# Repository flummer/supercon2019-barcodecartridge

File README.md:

# Barcode reader Cartridge for the 2019 Hackaday Superconference Badge

This is designed to use the GM65 barcode reader module, that supports both 1D and 2D barcodes and is able to read from a screen (eg. a smartphone or the screen on the badge)

This cartridge is based on the [unofficial Superconference 2019 Badge Cartridge template](https://github.com/flummer/supercon2019-cartridgetemplate) and hence include the w25q128 SPI flash and a 100nF cap in addition to the 2x20 pin angled male pin header for the badge connection. The flash allows badge configurations and firmware specific to this cartridge to be loaded from the cartridge it self making it selfcontained.

## Version 1.2 update

This updated version fixes an error in the pin connections on the cartridge connector (the two columns was flipped for some signals).

## Special note about the original version

If you want to use a PCB based on the original version with incorrect connections, it is possible to make a hardware hack on the 20x2 angeled header, where you move the pins around and bend some of them a bit, very precisely.

## License

The contents of this repository is released under the following licence:

 * the "Creative Commons Attribution-ShareAlike 4.0 International License"
   (CC BY-SA 4.0) full text of this license is included in the LICENSE file
   and a copy can also be found at
   http://creativecommons.org/licenses/by-sa/4.0/

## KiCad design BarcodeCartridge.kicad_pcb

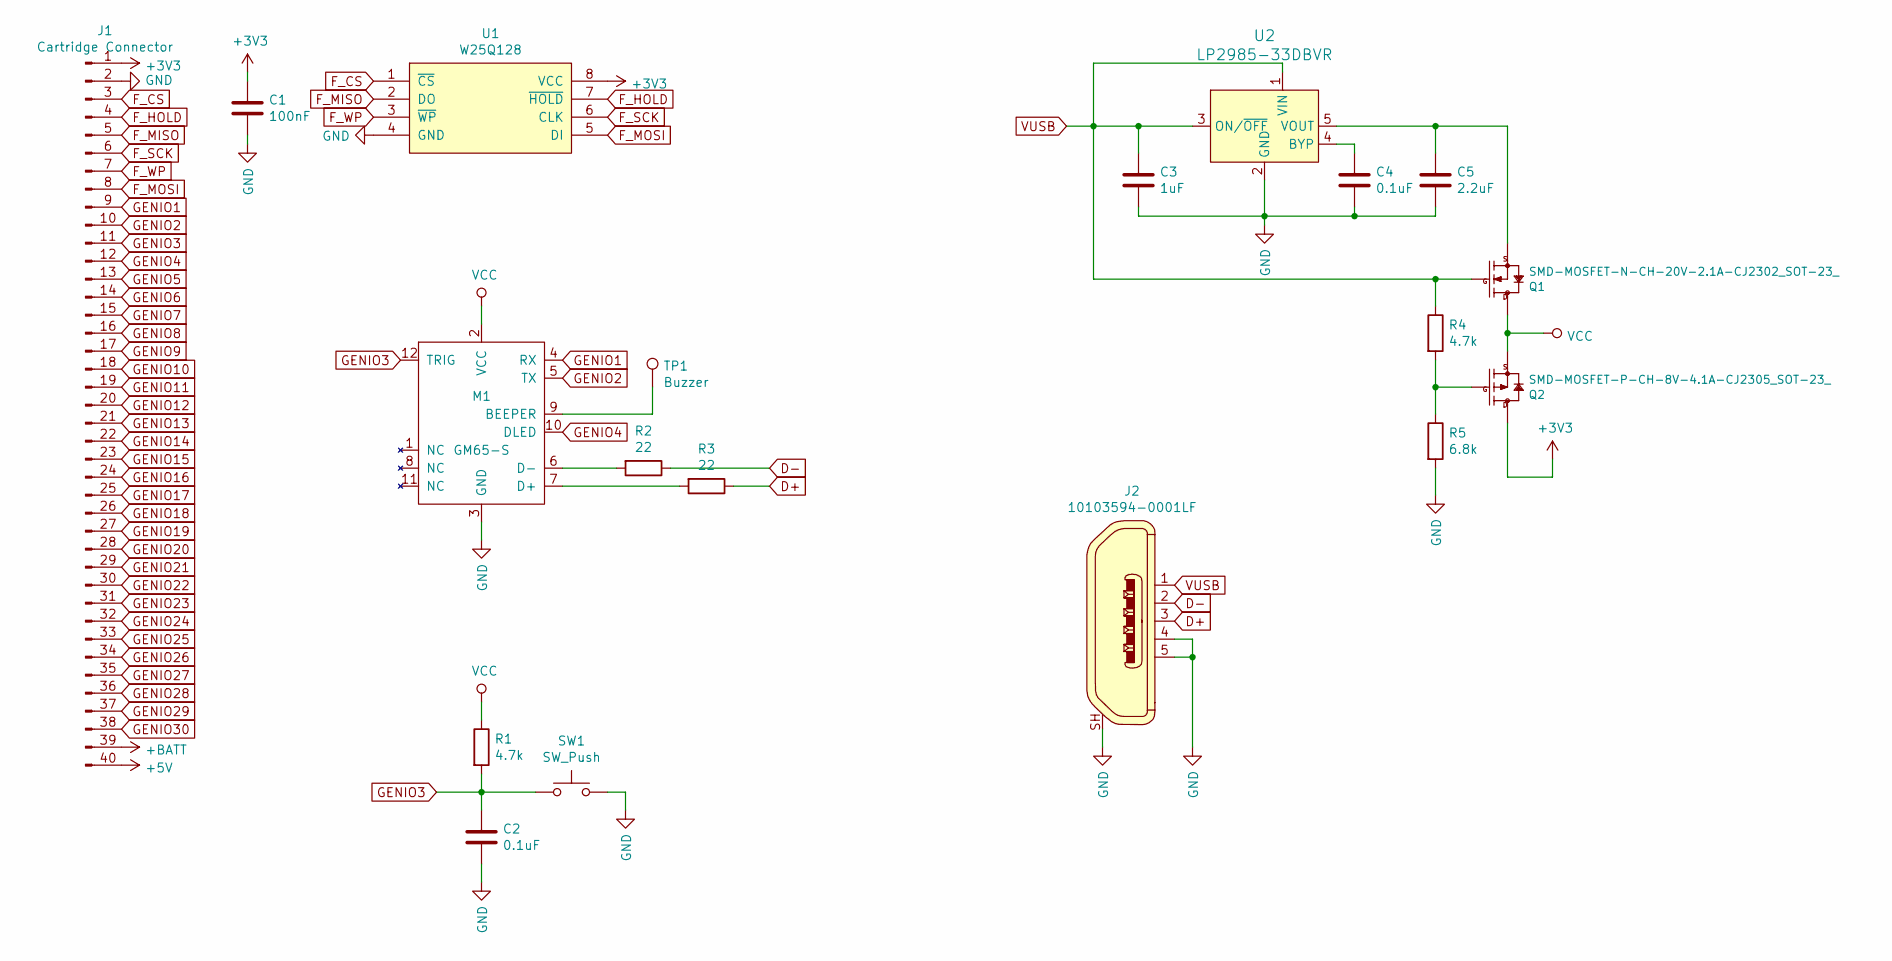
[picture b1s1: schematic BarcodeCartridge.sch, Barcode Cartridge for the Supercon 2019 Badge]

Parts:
C1: 100nF; C_0805_HandSoldering
C2, C4: 0.1uF; C_0805_HandSoldering
C3: 1uF; C_0805_HandSoldering
C5: 2.2uF; C_0805_HandSoldering
J1: Cartridge Connector; Supercon_Cartridge_40pin_Connector
J2: 10103594-0001LF; USB_Micro_B_Female_10103594-0001LF; MPN 10103594-0001LF; Digi-Key_PN 609-4050-1-ND
M1: GM65-S; SD-52892-044
Q1: SMD-MOSFET-N-CH-20V-2.1A-CJ2302_SOT-23_; SOT-23; MPN CJ2302
Q2: SMD-MOSFET-P-CH-8V-4.1A-CJ2305_SOT-23_; SOT-23; MPN CJ2305
R1, R4: 4.7k; R_0805_HandSoldering
R2, R3: 22; R_0805_HandSoldering
R5: 6.8k; R_0805_HandSoldering
SW1: SW_Push; SW_SPST_PTS645
TP1: Buzzer; Test_Point_Pad_d2.0mm
U1: W25Q128; SO-8_5.3x6.2mm_Pitch1.27mm
U2: LP2985-33DBVR; SOT-753; MPN LP2985-33DBVR; Digi-Key_PN 296-18476-1-ND

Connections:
+3V3: C1.1, J1.1, Q2.3 (D), U1.8 (VCC)
+5V: J1.40
+BATT: J1.39
D+: J2.3, R3.1
D-: J2.2, R2.1
F_CS: J1.3, U1.1 (~CS)
F_HOLD: J1.4, U1.7 (~HOLD)
F_MISO: J1.5, U1.2 (DO)
F_MOSI: J1.8, U1.5 (DI)
F_SCK: J1.6, U1.6 (CLK)
F_WP: J1.7, U1.3 (~WP)
GENIO1: J1.9, M1.4 (RX)
GENIO2: J1.10, M1.5 (TX)
GENIO3: C2.1, J1.11, M1.12 (TRIG), R1.2, SW1.1
GENIO4: J1.12, M1.10 (DLED)
GENIO5: J1.13
GENIO6: J1.14
GENIO7: J1.15
GENIO8: J1.16
GENIO9: J1.17
GENIO10: J1.18
GENIO11: J1.19
GENIO12: J1.20
GENIO13: J1.21
GENIO14: J1.22
GENIO15: J1.23
GENIO16: J1.24
GENIO17: J1.25
GENIO18: J1.26
GENIO19: J1.27
GENIO20: J1.28
GENIO21: J1.29
GENIO22: J1.30
GENIO23: J1.31
GENIO24: J1.32
GENIO25: J1.33
GENIO26: J1.34
GENIO27: J1.35
GENIO28: J1.36
GENIO29: J1.37
GENIO30: J1.38
GND: C1.2, C2.2, C3.2, C4.2, C5.2, J1.2, J2.4, J2.5, J2.SH, M1.3 (GND), R5.2, SW1.2, U1.4 (GND), U2.2 (GND)
unnamed: C4.1, U2.4 (BYP)
unnamed: C5.1, Q1.2 (S), U2.5 (VOUT)
unnamed: M1.6 (D-), R2.2
unnamed: M1.7 (D+), R3.2
unnamed: M1.9 (BEEPER), TP1.1
unnamed: Q2.1 (G), R4.2, R5.1
VCC: M1.2 (VCC), Q1.3 (D), Q2.2 (S), R1.1
VUSB: C3.1, J2.1, Q1.1 (G), R4.1, U2.1 (VIN), U2.3 (ON/~OFF)

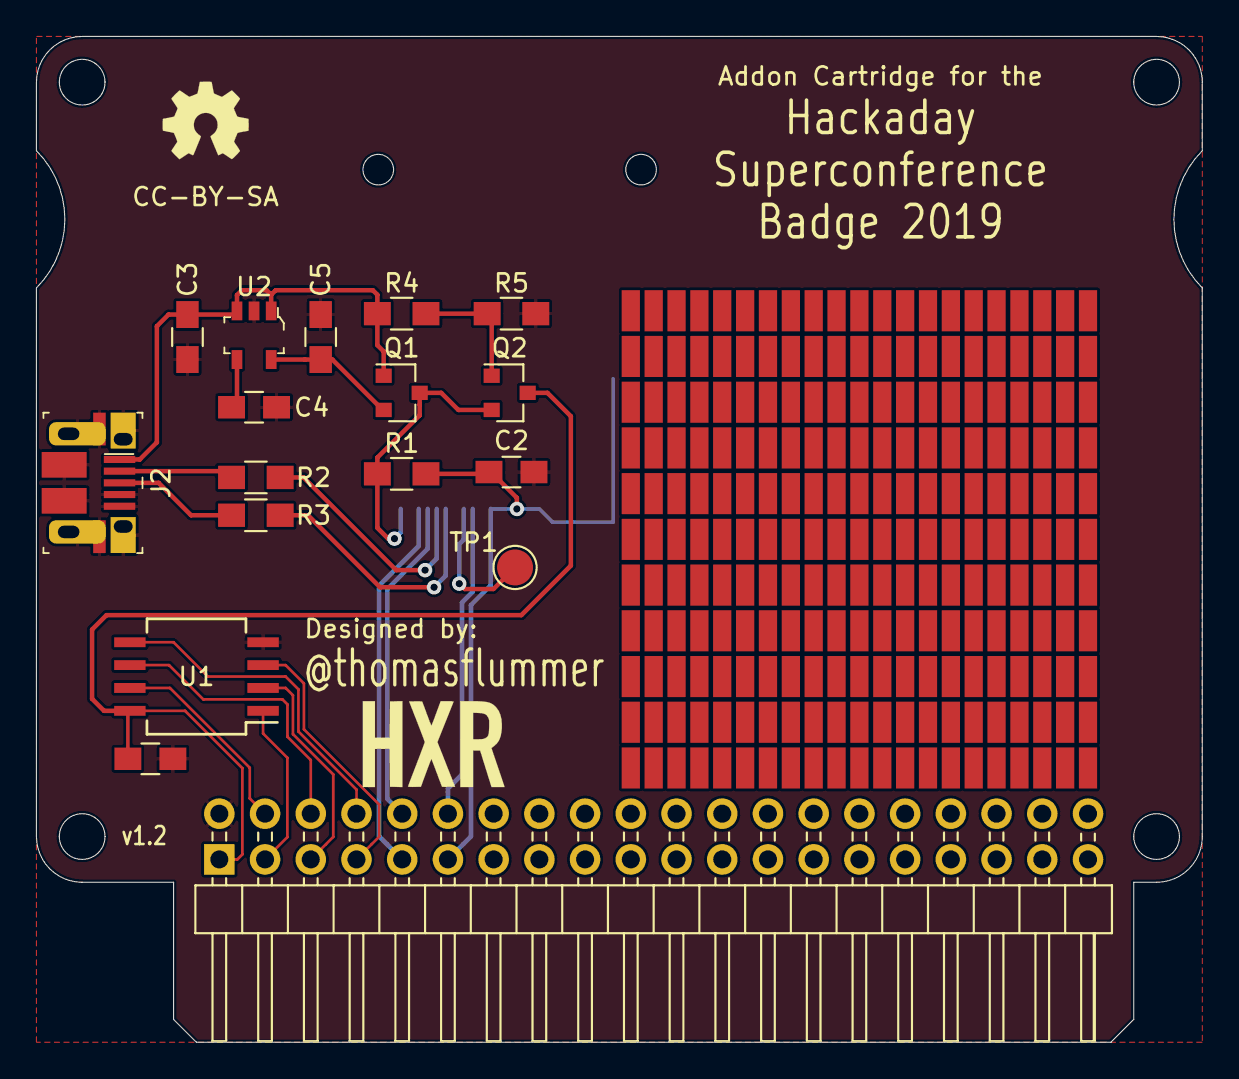
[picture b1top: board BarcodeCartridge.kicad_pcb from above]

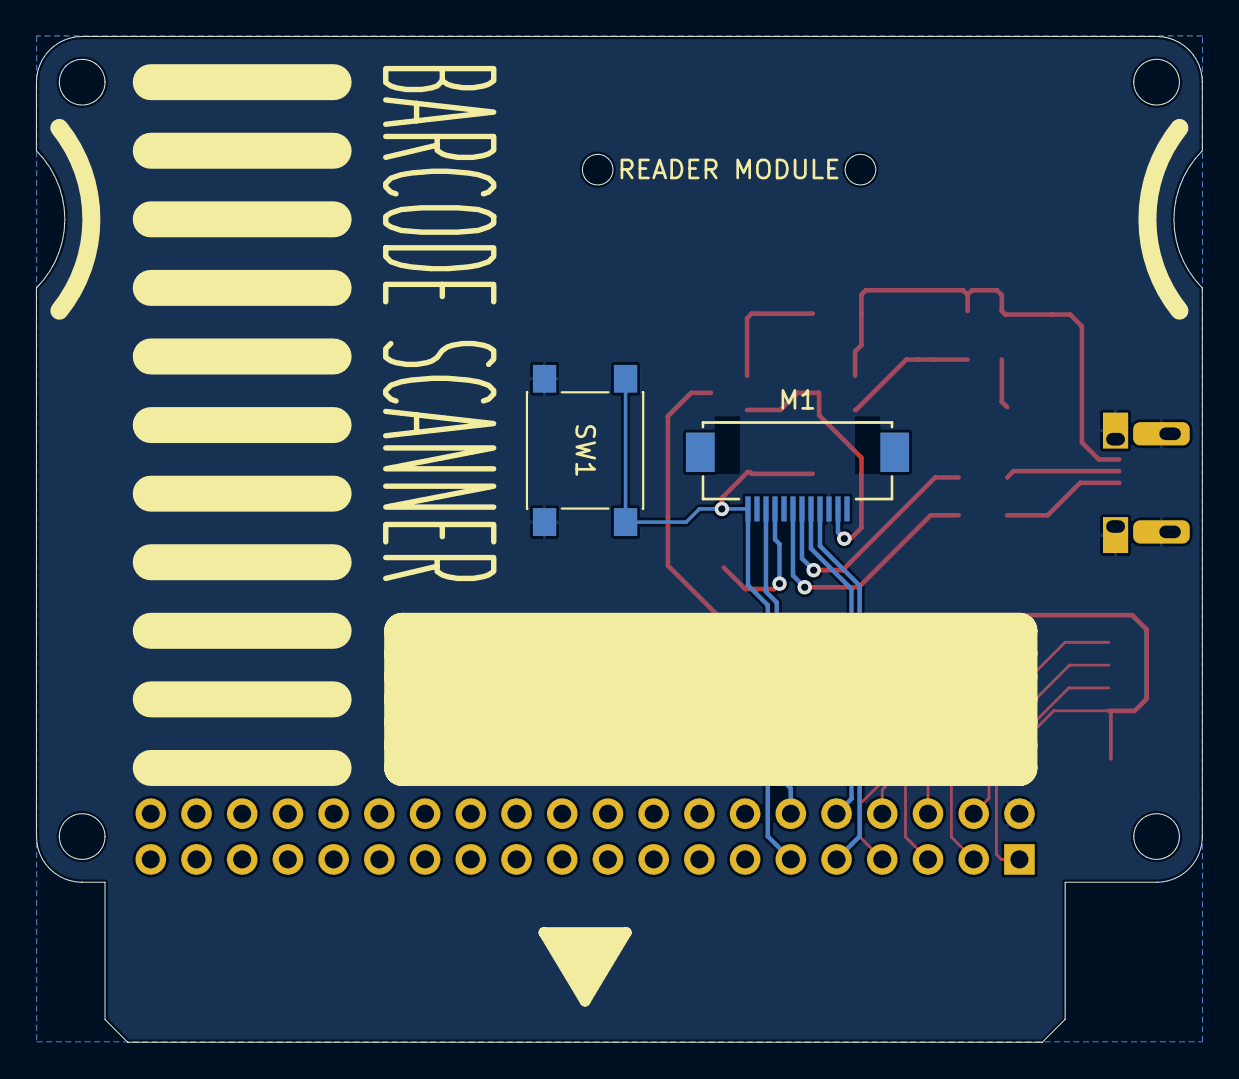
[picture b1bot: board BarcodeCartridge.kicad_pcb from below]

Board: 2 copper layers, 64.8 x 55.9 mm, 20 parts (3 on the bottom side), 22 nets.

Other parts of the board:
READER MODULE: GM65-S

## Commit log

2019-10-26 Renamed template files and updated README
2019-10-26 First design of the Barcode reader cartridge
    Also updated:
    - README
    - Render image
    - .gitignore
2019-10-29 Updated README and gerber export settings
2019-11-16 Fixed error in cartridge connector pin assignments
    Updated to version 1.2
